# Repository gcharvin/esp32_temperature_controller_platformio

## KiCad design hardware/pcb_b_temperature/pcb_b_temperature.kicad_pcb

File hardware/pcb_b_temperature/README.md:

# PCB B v0.5 — buck 5 V intégré

Révision courante B0.5.3 du 10 novembre 2026. Ouvrir `pcb_b_temperature.kicad_pro`, puis le
schéma ou `pcb_b_temperature.kicad_pcb`. La carte garde **90 × 65 × 1,6 mm**,
deux couches externes de cuivre **70 µm**, les réserves de clips et les positions
des connecteurs conservés. A reste à v0.4.

## Alimentation

```text
J2 24V → F1 → Q2 anti-inversion → VIN_PROTECTED → J3 chauffage
                                   │
                                   └→ U1 LM2596 → L1 → +5V_BUCK → F2 1A → J1/A et logique B
                                                  │
                                                  └→ C10 → R13 → PGND

PGND puissance ── NT1, jonction cuivre près de l'entrée ── GND logique
```

| Repère | Élément | Empreinte / rôle |
| --- | --- | --- |
| U1 | LM2596S-5.0/NOPB | TO-263-5, languette **broche 3 / PGND** |
| L1 | Bourns SRP1770TA-101M, 100 µH | 16,9 × 16,9 mm, hauteur 7 mm |
| D9 | Vishay SS36-E3/57T, 60 V / 3 A | SMC, cathode sur BUCK_SW |
| C8 | Panasonic EEUFR1H101, 100 µF / 50 V | Condensateur d'entrée existant, déplacé ; Ø8 mm, pas 3,5 mm |
| C9 | 100 nF / 50 V X7R | 0805, découplage d'entrée local |
| C10 | Panasonic EEUFS1V331LB, 330 µF / 35 V | Ø8 mm nominal, pas formé 5 mm, hauteur maximale 16,5 mm ; dégagement Ø10 conservé |
| R13 | Vishay WSL1206R0500FEA, 50 mΩ / 1 % / 0,25 W | Empreinte locale `LabHardware:Vishay_WSL1206_6m_to_200m`, **dans le retour du condensateur C10**, pas en série avec la charge |
| NT1 | NetTie-2_SMD_Pad2.0mm | Cuivre de liaison des masses, exclu de la BOM d'assemblage |

La revue de fabrication adapte les pastilles R13 au dessin Vishay :
1,65 × 1,93 mm, centres espacés de 3,45 mm, intervalle intérieur 1,80 mm.
R13 est légèrement déplacée, de (20,5 ; 45) à (21 ; 44,5) mm dans le repère
local du PCB, pour dégager les zones de C10 et F2. Les pistes existantes restent
connectées dans les nouvelles plages. Les contrôles DRC et de démontage
mécanique ont été régénérés. Voir le [dossier de fabrication](../manufacturing/README.md)
et son plan d'assemblage pour les polarités et les coordonnées.

J8 et J9 et le module XL4015 sont supprimés. U1 a une sortie fixe 5 V : aucune
consigne à régler. Sa broche 5 ON/OFF est reliée à PGND ; le buck est activé
avec le 24 V. La limite étudiée est **0,8 A pour le système** ; F2 reste à 1 A.
La revue d'approvisionnement propose C9 **C0805C104K5RACTU** et R13
**WSL1206R0500FEA**. Leurs caractéristiques nominales correspondent aux
exigences ; disponibilité, pastilles recommandées et procédé restent à
approuver dans `../manufacturing/README.md` avant gel des MPN dans KiCad.

A reçoit toujours 5 V régulé. Les futures B pourront recevoir 12 V ou 5 V
avec leur propre adaptation d'alimentation ; cette B v0.5 n'est pas déclarée
multitension. Le démarrage du cœur du buck à 12 V est étudié séparément ;
aucune puissance de chauffage 100 W à 12 V/5 V n'est attribuée à cette carte.
Voir `../manufacturing/power_and_usb_review.md`.

Les masses gardent deux noms pour organiser leurs retours. NT1 les relie
électriquement près de l'entrée ; ce n'est pas une isolation. Le trajet du
chauffage jusqu'à J2 reste sur sa piste PGND de puissance, sans passer dans
NT1, les JST ou la DevKit. Les cinq trajets principaux de chauffage sont
contrôlés géométriquement et restent sans via discret.

## Placement, routage et contrôle

Le buck occupe la partie gauche et centrale de B. Plusieurs composants de
logique et voyants sont déplacés. Les JST A/B J1/J6/J7, la sonde J4 et les
borniers J2/J3 gardent leurs positions et brochages. `../placement.json` décrit
le placement courant et les hauteurs, sans enveloppes provisoires sans pads.

Le schéma natif, la BOM et le routage sont mis à jour ensemble. Résultat des
contrôles : **ERC 0 erreur / 0 avertissement, DRC 0 violation, 0 connexion
restante, 0 écart schéma/PCB**. Le rapport du buck et la conservation des
connecteurs sont dans `../review/routing/integrated_buck_validation.json`.
Les PDF de revue sont `../review/pcb_b_temperature.pdf` et
`../review/routing/pcb_b_temperature_routed.pdf`.

Le routage des boucles de commutation est explicite, avec un plan PGND local
sous la languette thermique. Les liaisons restantes ont été amorcées localement
avec Freerouting 1.9.0 en mode **un seul thread**, analytics désactivées, puis
corrigées et contrôlées dans KiCad. Aucune API de routage distante n'a reçu la
carte. Les scripts de migration sont des étapes historiques à appliquer à une
copie de v0.4 ; ils ne régénèrent pas les fichiers natifs livrés après édition.

## Simulation et limites

Le circuit de puissance reprend l'[étude LM2596](../power_study/lm2596/README.md) :
six essais d'acceptation complets sous ngspice, plus deux sensibilités ESR.
C8 fournit les 100 µF d'entrée étudiés ; C9 ajoute le découplage HF. Le banc
représente les ESR/DCR, mais pas les parasites des pistes, vias, connecteurs,
la protection amont ni le couplage du PWM chauffage. Le rattachement des nets
et les valeurs principales sont contrôlés sur la netlist exportée de B ; la
simulation n'est pas une extraction parasite du PCB routé.

La pointe de démarrage simulée approche **4,9 A dans L1**. Saturation réelle,
diode, fusibles, transitoires d'entrée, thermique, bruit sur la NTC et défauts
restent à vérifier sur prototype. Ce n'est pas un dossier libéré pour fabrication.
Le partage USB/VBUS et la mise à jour du firmware restent des sujets distincts.

**Mécanique :** le [STEP v0.8](../mechanical/README.md) représente maintenant ce
placement de B et ses hauteurs. Le berceau du XL4015 est retiré ; quatre pièces
imprimées et 17 étapes de montage/service passent les contrôles géométriques.
J1 reste proche de C10 : la fiche XHP documentée et sa marge passent, mais la
prise en main, les fils, la flexion des clips et la thermique exigent des essais
réels. Voir le [plan de mise au point](../review/routing/electronics_bench_plan.md).

Sources : [TI LM2596](https://www.ti.com/lit/ds/symlink/lm2596.pdf),
[Bourns SRP1770TA](https://www.bourns.com/docs/Product-Datasheets/srp1770ta.pdf),
[Vishay SS36](https://www.vishay.com/docs/88751/ss32.pdf),
[Panasonic C10](https://industrial.panasonic.com/ww/products/pt/aluminum-cap-lead/models/EEUFS1V331LB).

La préparation3 fige les MPN dans KiCad, emploie les pastilles Kingbright pour les voyants et décale D7 de0,25mm en Y pour dégager SDA. Les borniers sont modélisés à14mm de hauteur enveloppe. Les valeurs électriques et les pistes sont conservées. Les instructions de câblage, de test et d’assemblage sont dans le dossier de fabrication.

## Révision diagnostic du 6 novembre 2026

Les pastilles TP au dos sont du cuivre seul, sans pâte ni pièce à acheter.
Voir [le plan de mesure](../TEST_POINTS.md) et le firmware autonome dans
`../../firmware/diagnostic/`. Les pistes antérieures et le circuit de puissance
sont conservés ; le diagnostic maintient ENABLE à zéro.

## Extension UART du 10 novembre 2026

Révisions **A0.4.3 / B0.5.3** : J10 est un JST-XH3 supplémentaire assemblé
sur chaque PCB, pas2,50mm, même MPN B3B-XH-A(LF)(SN) que J6.

| Broche J10 | Carte A | Carte B température |
| --- | --- | --- |
| 1 | GND | GND |
| 2 | TX_A, GPIO17, pad U1.22 | Non connectée ; réserve RX de future B |
| 3 | RX_A, GPIO16, pad U1.21 | Non connectée ; réserve TX de future B |

Câblage **droit 1→1, 2→2, 3→3** ; TX/RX sont nommés du point de vue de A.
UART logique **3,3V**, sans alimentation dans ce connecteur : jamais RS232
ni5V directement. Les transceivers RS232/RS485 éventuels appartiennent aux
futures B. Le port série USB de la DevKit reste indépendant ; les deux PWM
et ENABLE/FAULT_N/DIN0 restent disponibles. GPIO16/17 doivent être libres
sur la variante de DevKit employée (modules à PSRAM utilisant ces broches
non couverts par cette interface). Aucun UART n’est activé par le firmware
de diagnostic actuel ; aucun essai de boucle matérielle n’est déclaré fait.

B température n’a pas de périphérique UART : les deux pastilles sont
intentionnellement NC et le connecteur est néanmoins à souder. Le câble UART
est **facultatif pour ce prototype** et n’est pas ajouté au devis LCSC en cours.
Si nécessaire plus tard, reprendre la construction H02 XHP-3/XHP-3,300mm AWG26
avec un repérage UART distinct. Ne pas confondre J6 I²C et J10 UART, mécaniquement
identiques. Les alias fabricant J8/J9 des deux sockets de A restent inchangés.

## B0.5.3 : variantes du devis intégrées

C10 utilise maintenant `LabHardware:CP_Radial_EEUFS1V331LB_P5_D10_Keepout` :
les pastilles, trous et dégagement Ø10 antérieurs sont conservés ; le modèle
3D local a une hauteur maximale de 16,5 mm. R13 = 50 mΩ dans le retour de C10.
D8 HEAT est jaune ; ses pastilles et sa résistance de 2,2 kΩ sont conservées.
Les sept essais électriques de la combinaison FS/50 mΩ passent ; voir
`../power_study/lm2596/current_acceptance.json`. Le STEP courant est v12.
Les pistes, vias, UUID de pastilles, positions et nets n'ont pas changé.

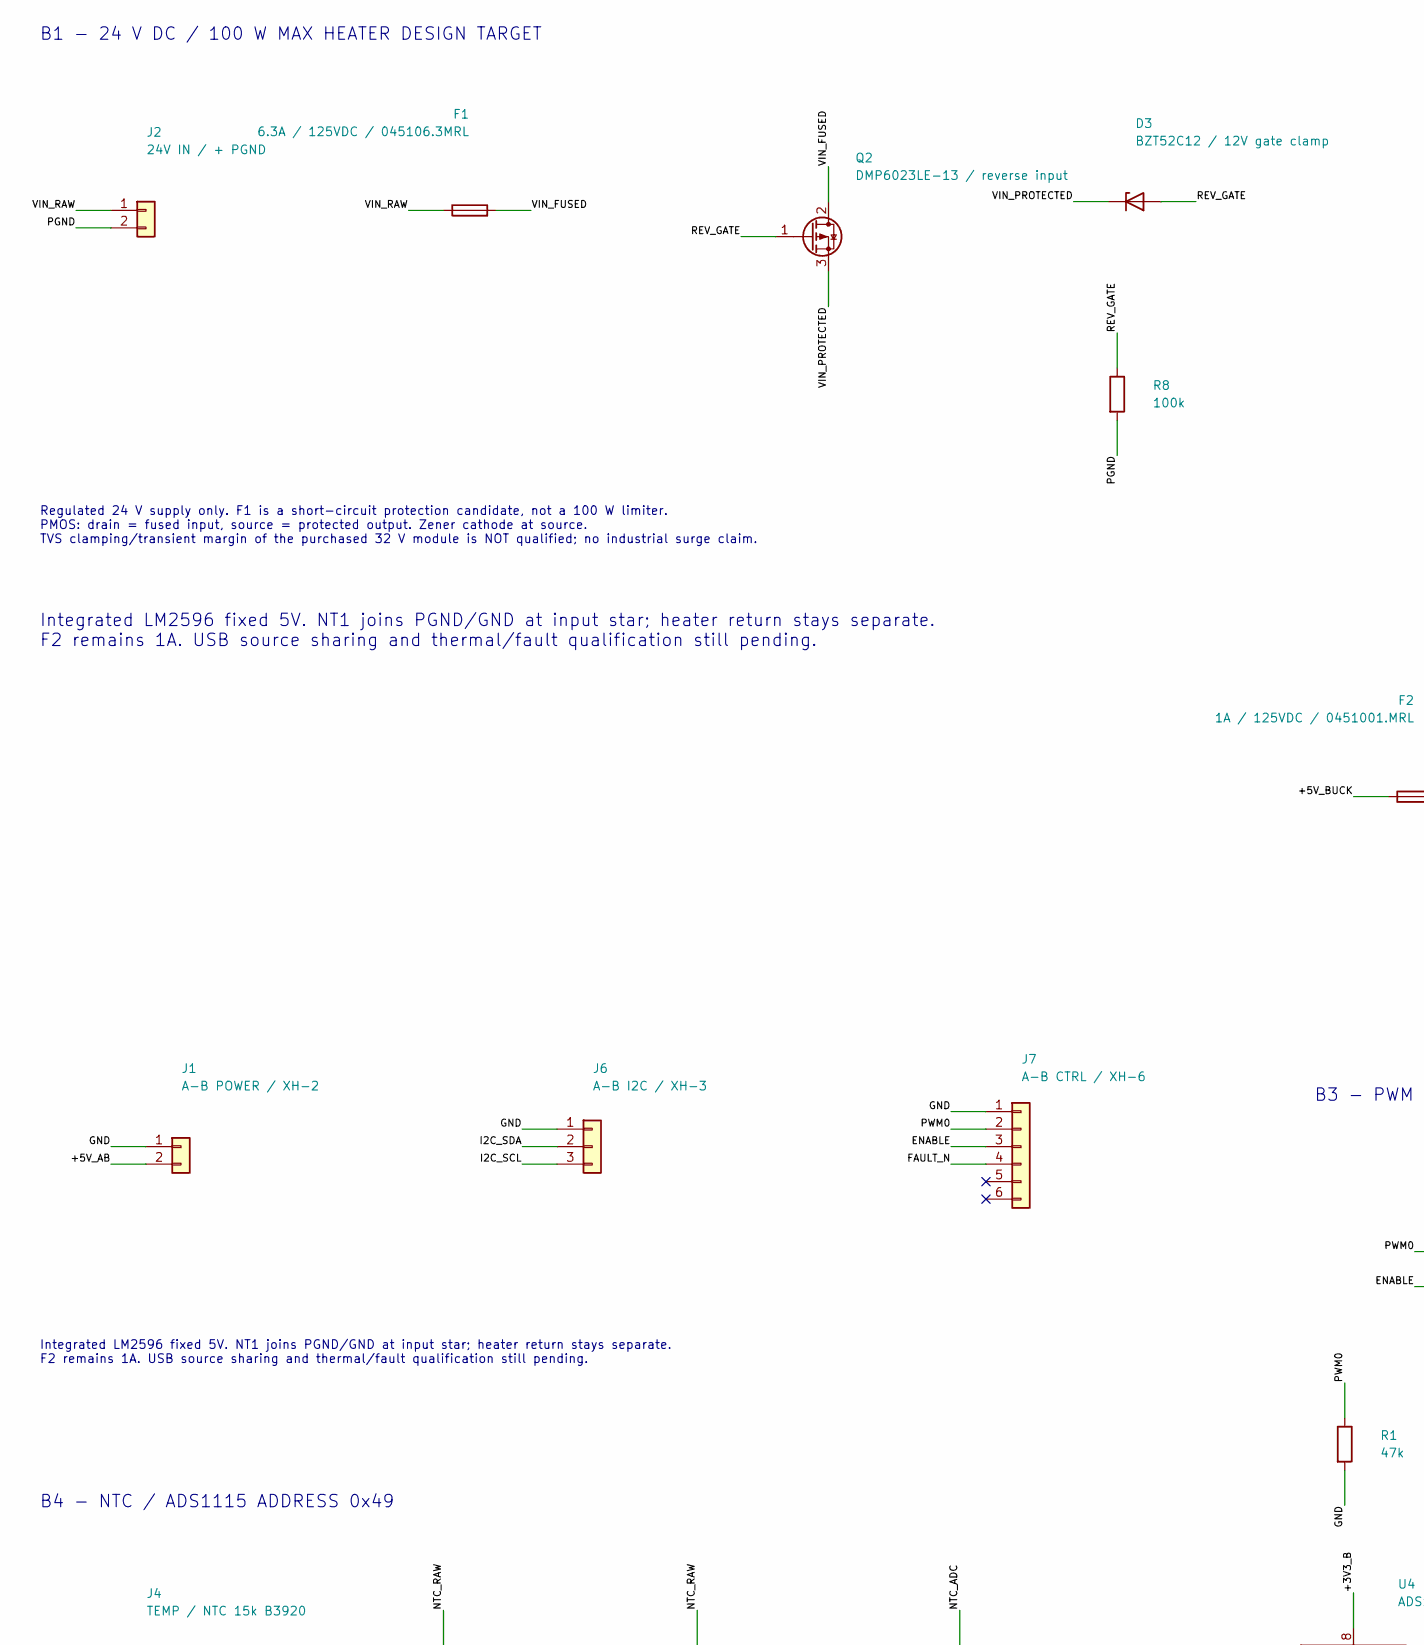
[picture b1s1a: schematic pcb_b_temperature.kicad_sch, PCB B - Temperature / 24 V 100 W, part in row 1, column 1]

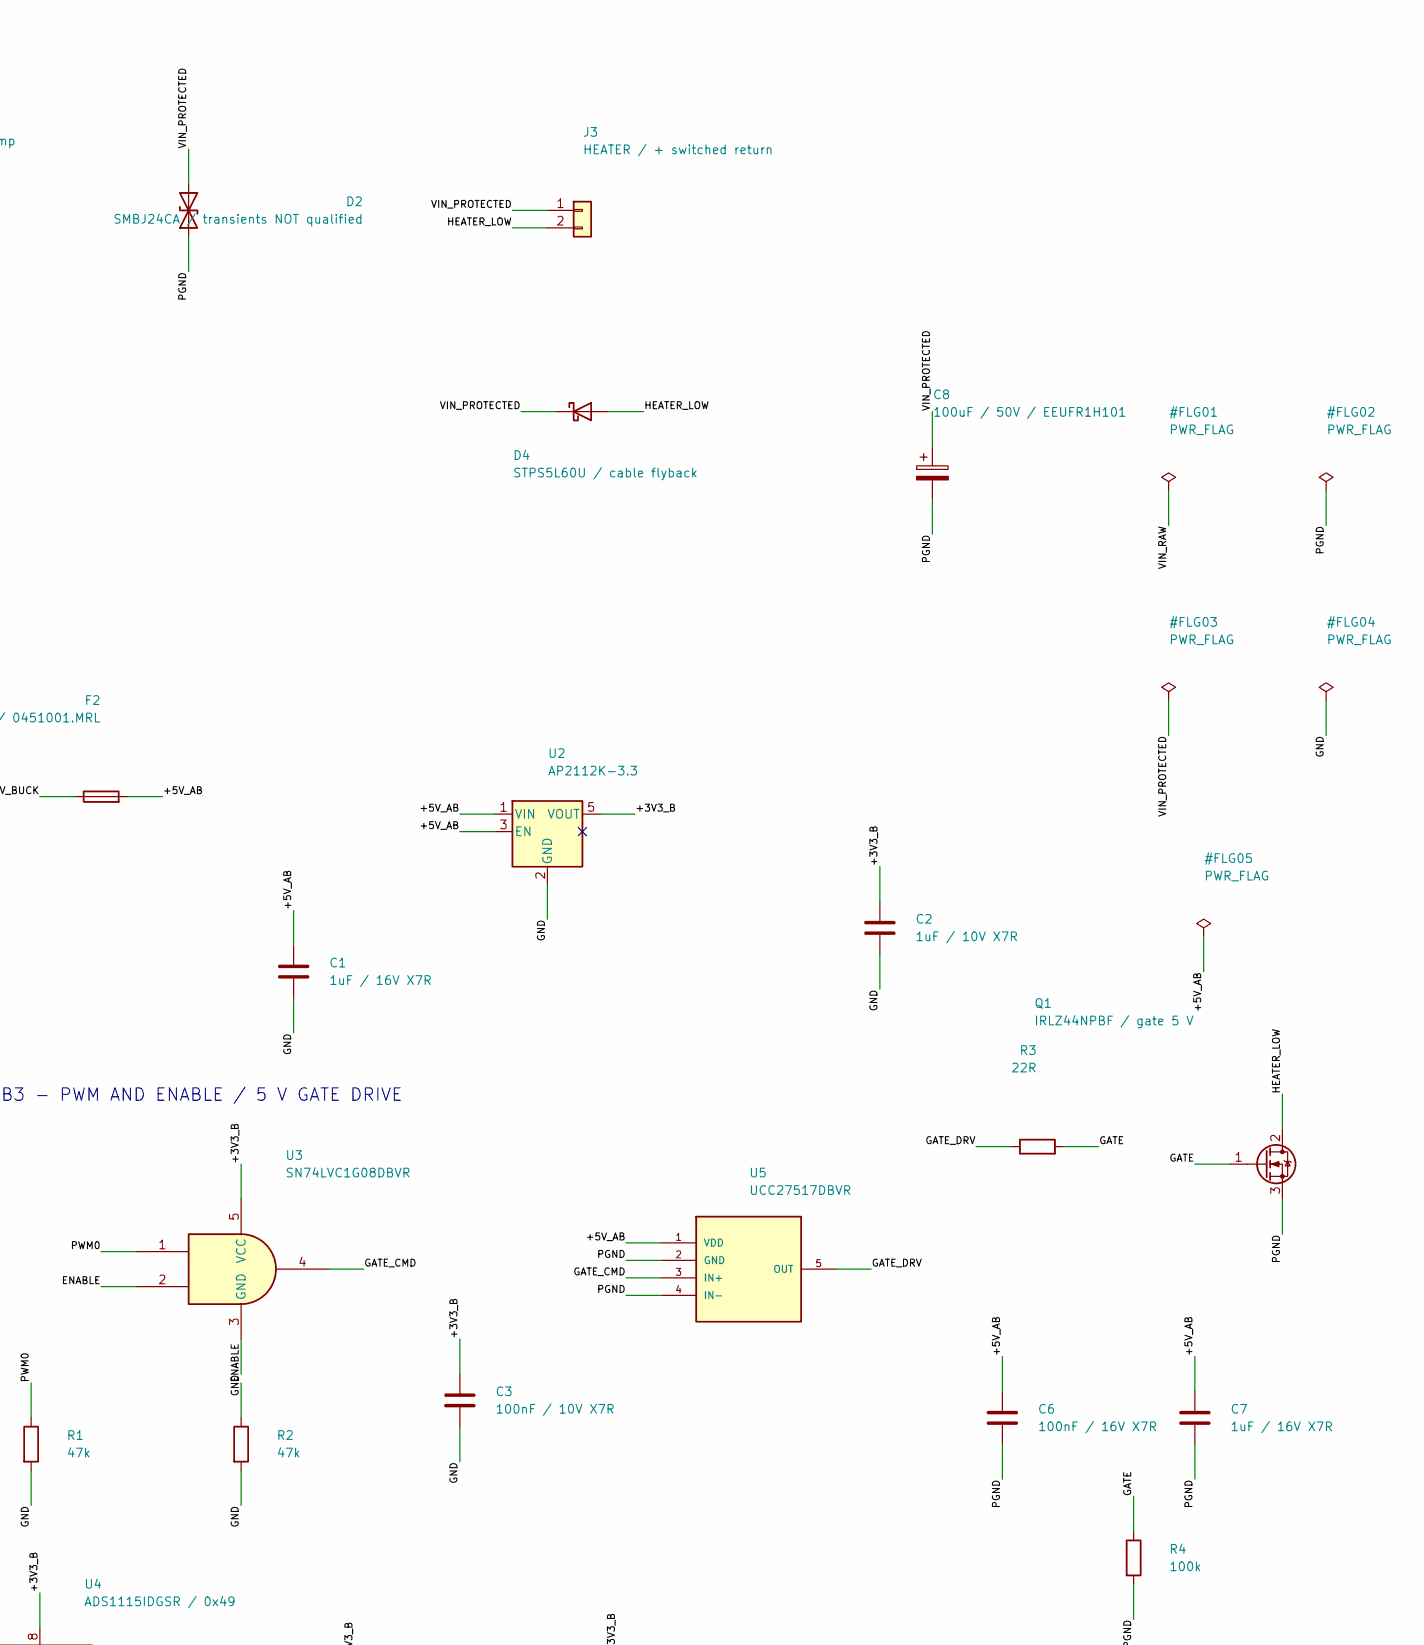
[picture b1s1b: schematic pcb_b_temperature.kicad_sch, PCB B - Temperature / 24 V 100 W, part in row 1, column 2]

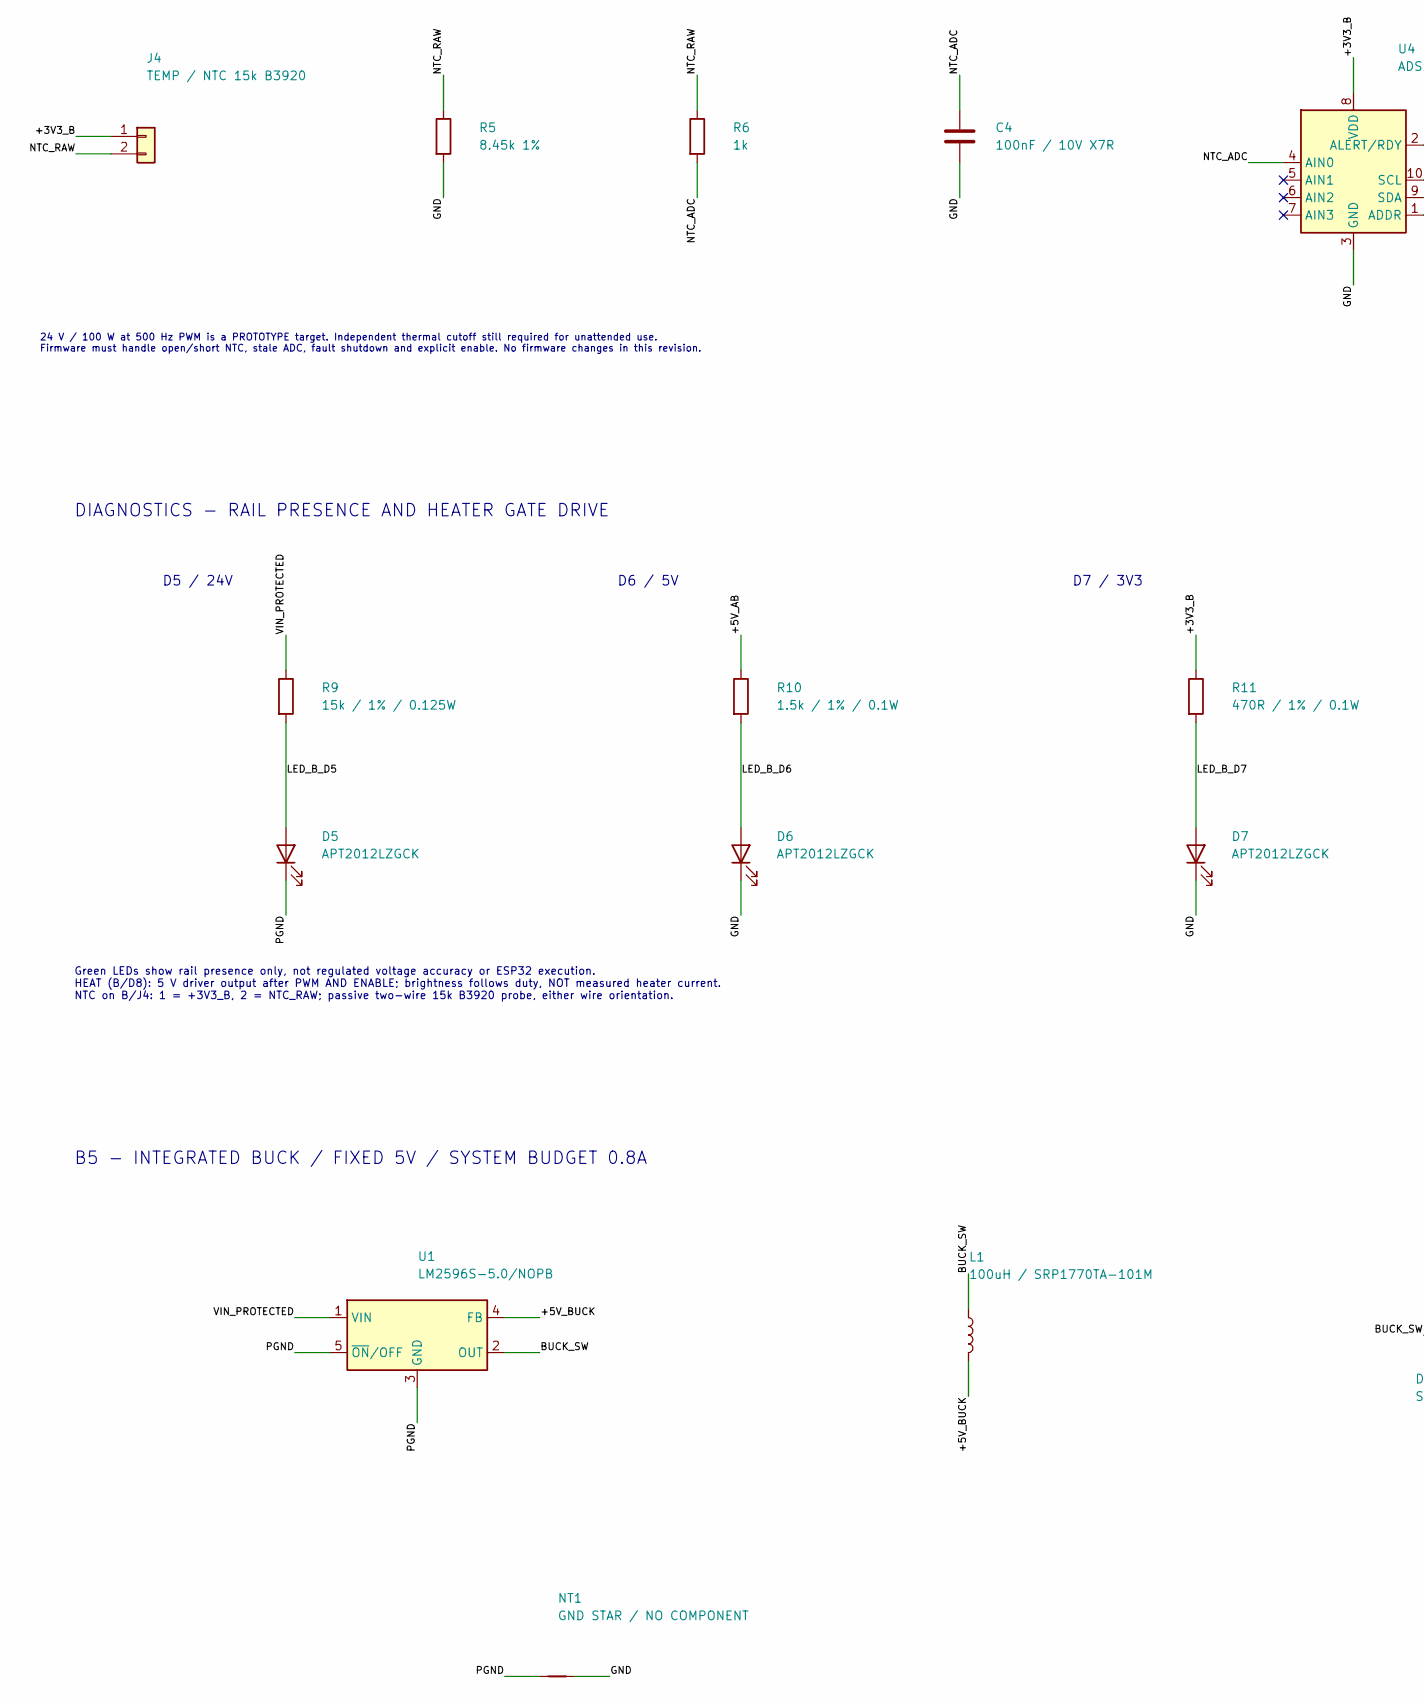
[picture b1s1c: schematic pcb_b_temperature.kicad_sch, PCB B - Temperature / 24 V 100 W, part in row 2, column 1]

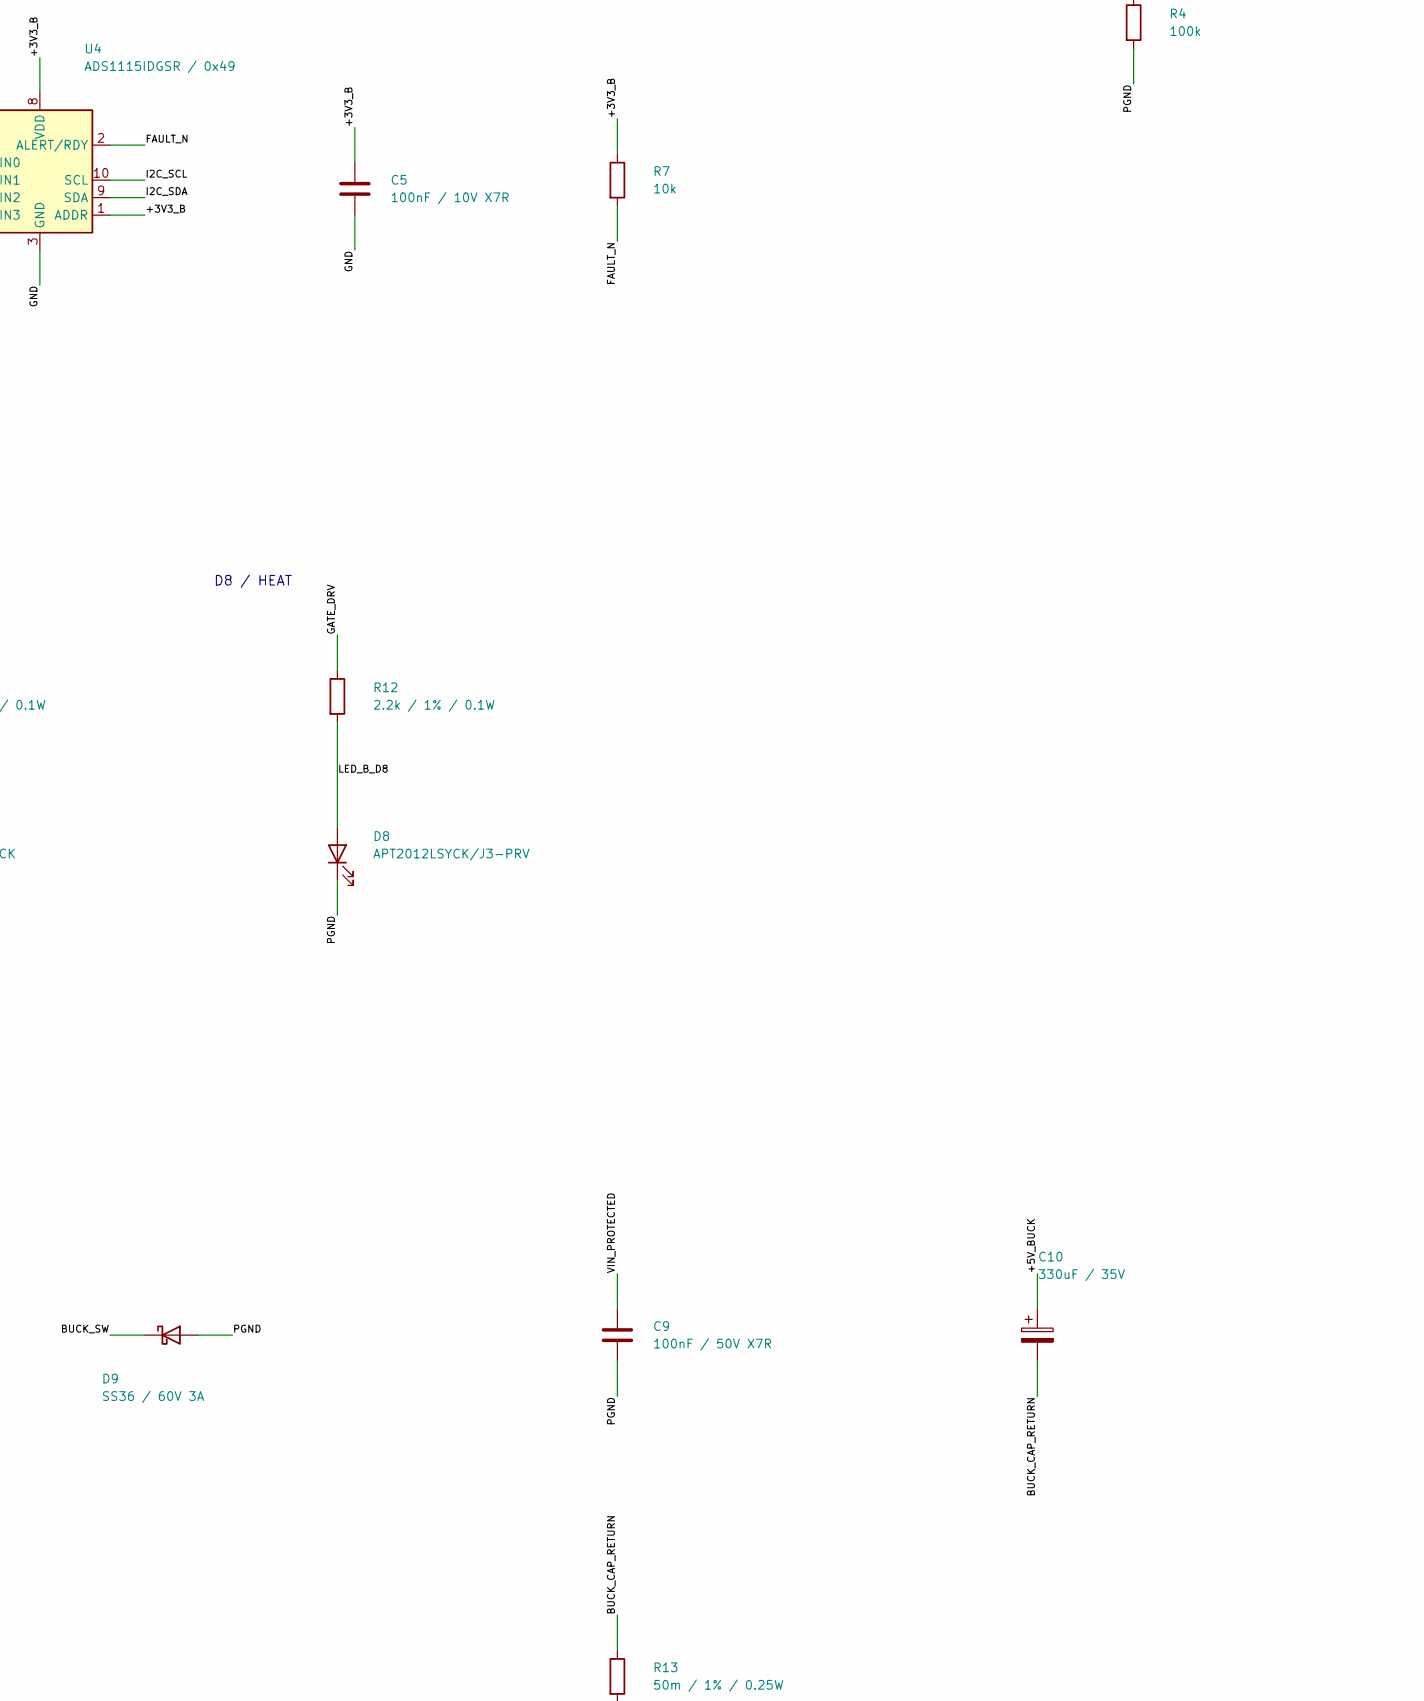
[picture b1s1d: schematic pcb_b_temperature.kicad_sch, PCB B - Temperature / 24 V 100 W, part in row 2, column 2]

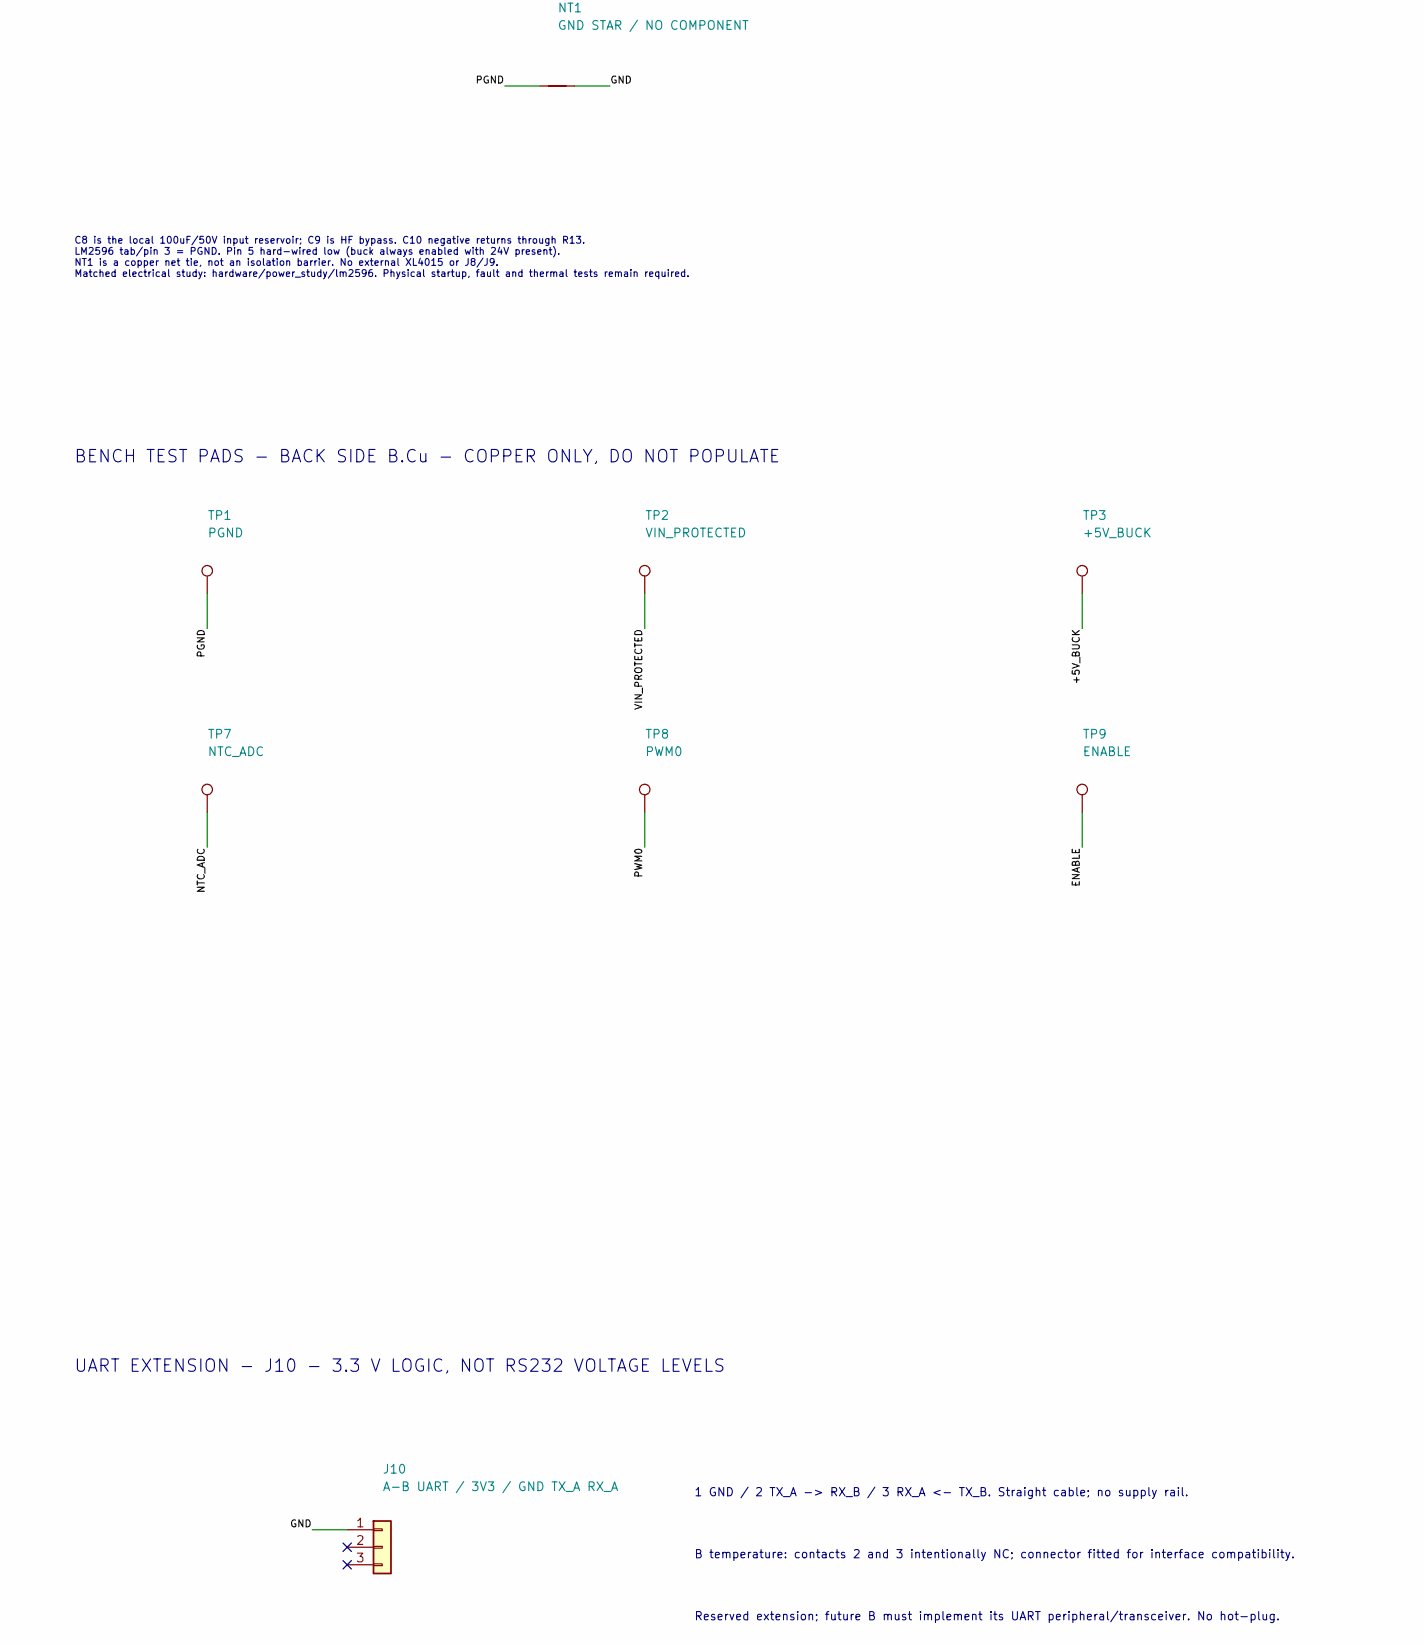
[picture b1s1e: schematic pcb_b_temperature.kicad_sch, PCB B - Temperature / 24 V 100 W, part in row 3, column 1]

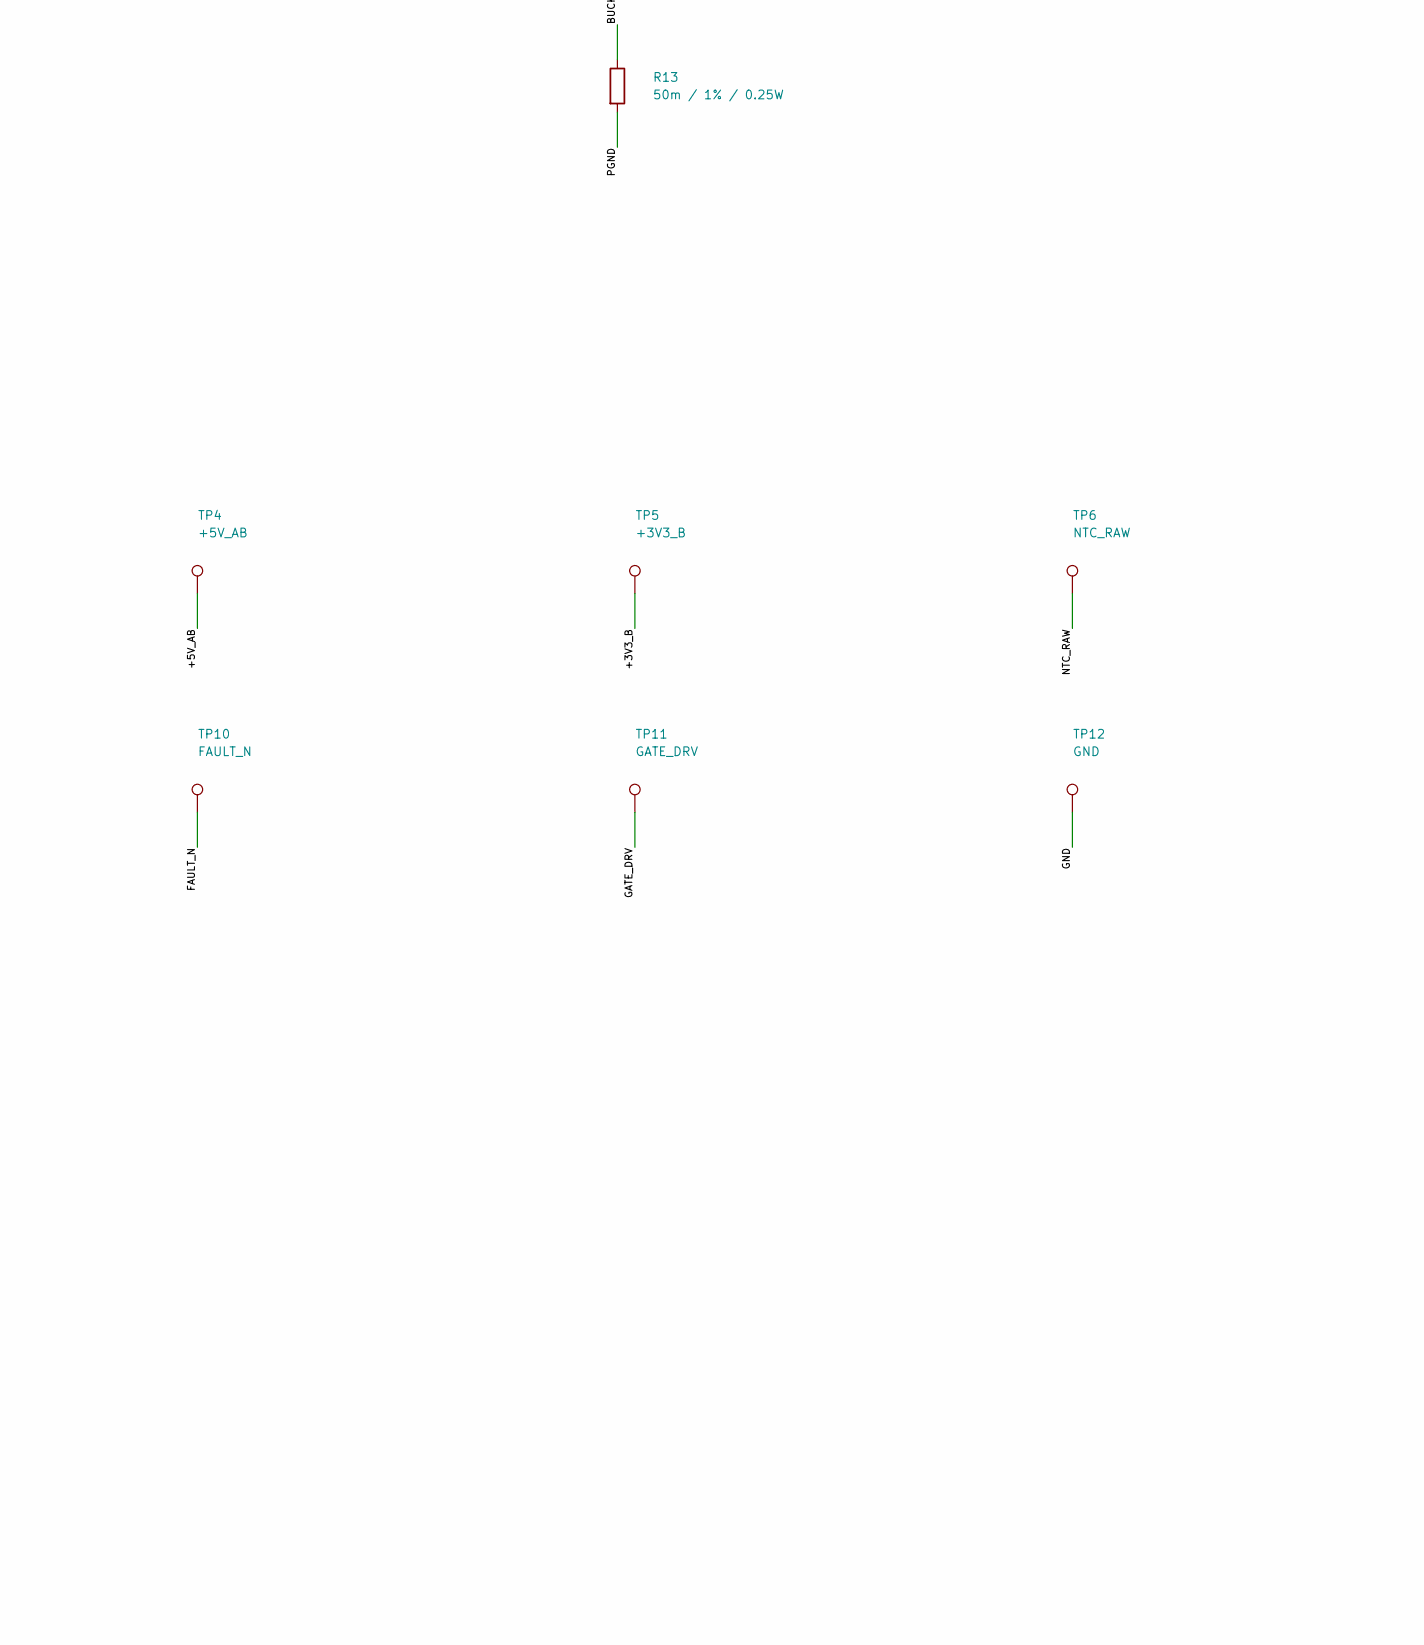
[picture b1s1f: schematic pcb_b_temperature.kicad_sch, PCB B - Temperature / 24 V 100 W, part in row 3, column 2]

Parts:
C1, C7: 1uF / 16V X7R; C_0603_1608Metric; MPN 0603B105K160CT
C2: 1uF / 10V X7R; C_0603_1608Metric; MPN 0603B105K160CT
C3, C4, C5: 100nF / 10V X7R; C_0603_1608Metric; MPN C0603C104K4RACTU
C6: 100nF / 16V X7R; C_0603_1608Metric; MPN C0603C104K4RACTU
C8: 100uF / 50V / EEUFR1H101; CP_Radial_D8.0mm_P3.50mm; MPN EEUFR1H101
C9: 100nF / 50V X7R; C_0805_2012Metric; MPN C0805C104K5RACTU
C10: 330uF / 35V; CP_Radial_EEUFS1V331LB_P5_D10_Keepout; MPN EEUFS1V331LB
D2: SMBJ24CA / transients NOT qualified; D_SMB; MPN SMBJ24CA
D3: BZT52C12 / 12V gate clamp; D_SOD-123; MPN BZT52C12-7-F
D4: STPS5L60U / cable flyback; D_SMB; MPN STPS5L60U
D5, D6, D7: APT2012LZGCK; LED_Kingbright_APT2012_Manufacturer; MPN APT2012LZGCK
D8: APT2012LSYCK/J3-PRV; LED_Kingbright_APT2012_Manufacturer; MPN APT2012LSYCK/J3-PRV
D9: SS36 / 60V 3A; D_SMC; MPN SS36-E3/57T
F1: 6.3A / 125VDC / 045106.3MRL; Fuse_Littelfuse-NANO2-451_453; MPN 045106.3MRL
F2: 1A / 125VDC / 0451001.MRL; Fuse_Littelfuse-NANO2-451_453; MPN 0451001.MRL
J1: A-B POWER / XH-2; JST_XH_B2B-XH-A_1x02_P2.50mm_Vertical; MPN B2B-XH-A(LF)(SN)
J2: 24V IN / + PGND; TerminalBlock_Phoenix_MKDS-1,5-2-5.08_1x02_P5.08mm_Horizont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; MPN 1715721
J3: HEATER / + switched return; TerminalBlock_Phoenix_MKDS-1,5-2-5.08_1x02_P5.08mm_Horizont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; MPN 1715721
J4: TEMP / NTC 15k B3920; JST_XH_B2B-XH-A_1x02_P2.50mm_Vertical; MPN B2B-XH-A(LF)(SN)
J6: A-B I2C / XH-3; JST_XH_B3B-XH-A_1x03_P2.50mm_Vertical; MPN B3B-XH-A(LF)(SN)
J7: A-B CTRL / XH-6; JST_XH_B6B-XH-A_1x06_P2.50mm_Vertical; MPN B6B-XH-A(LF)(SN)
J10: A-B UART / 3V3 / GND TX_A RX_A; JST_XH_B3B-XH-A_1x03_P2.50mm_Vertical; MPN B3B-XH-A(LF)(SN)
L1: 100uH / SRP1770TA-101M; L_Bourns_SRP1770TA_16.9x16.9mm; MPN SRP1770TA-101M
NT1: GND STAR / NO COMPONENT; NetTie-2_SMD_Pad2.0mm
Q1: IRLZ44NPBF / gate 5 V; TO-220-3_Vertical; MPN IRLZ44NPBF
Q2: DMP6023LE-13 / reverse input; SOT-223-3_TabPin2; MPN DMP6023LE-13
R1, R2: 47k; R_0603_1608Metric; MPN RC0603FR-0747KL
R3: 22R; R_0603_1608Metric; MPN RC0603FR-0722RL
R4, R8: 100k; R_0603_1608Metric; MPN RC0603FR-07100KL
R5: 8.45k 1%; R_0603_1608Metric; MPN RC0603FR-078K45L
R6: 1k; R_0603_1608Metric; MPN RC0603FR-071KL
R7: 10k; R_0603_1608Metric; MPN RC0603FR-0710KL
R9: 15k / 1% / 0.125W; R_0805_2012Metric; MPN RC0805FR-0715KL
R10: 1.5k / 1% / 0.1W; R_0603_1608Metric; MPN RC0603FR-071K5L
R11: 470R / 1% / 0.1W; R_0603_1608Metric; MPN RC0603FR-07470RL
R12: 2.2k / 1% / 0.1W; R_0603_1608Metric; MPN RC0603FR-072K2L
R13: 50m / 1% / 0.25W; Vishay_WSL1206_6m_to_200m; MPN WSL1206R0500FEA
TP1: PGND; ProbePad_D1.5mm_NoPaste
TP2: VIN_PROTECTED; ProbePad_D1.5mm_NoPaste
TP3: +5V_BUCK; ProbePad_D1.5mm_NoPaste
TP4: +5V_AB; ProbePad_D1.5mm_NoPaste
TP5: +3V3_B; ProbePad_D1.5mm_NoPaste
TP6: NTC_RAW; ProbePad_D1.5mm_NoPaste
TP7: NTC_ADC; ProbePad_D1.5mm_NoPaste
TP8: PWM0; ProbePad_D1.5mm_NoPaste
TP9: ENABLE; ProbePad_D1.5mm_NoPaste
TP10: FAULT_N; ProbePad_D1.5mm_NoPaste
TP11: GATE_DRV; ProbePad_D1.5mm_NoPaste
TP12: GND; ProbePad_D1.5mm_NoPaste
U1: LM2596S-5.0/NOPB; TO-263-5_TabPin3; MPN LM2596S-5.0/NOPB
U2: AP2112K-3.3; SOT-23-5; MPN AP2112K-3.3TRG1
U3: SN74LVC1G08DBVR; SOT-23-5; MPN SN74LVC1G08DBVR
U4: ADS1115IDGSR / 0x49; TSSOP-10_3x3mm_P0.5mm; MPN ADS1115IDGSR
U5: UCC27517DBVR; SOT-23-5; MPN UCC27517DBVR

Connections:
/+3V3_B: C2.1, C3.1, C5.1, J4.1, R7.1, R11.1, TP5.1, U2.5 (VOUT), U3.5 (VCC), U4.1 (ADDR), U4.8 (VDD)
/+5V_AB: C1.1, C6.1, C7.1, F2.2, J1.2, R10.1, TP4.1, U2.1 (VIN), U2.3 (EN), U5.1 (VDD)
/+5V_BUCK: C10.1, F2.1, L1.2, TP3.1, U1.4 (FB)
/BUCK_CAP_RETURN: C10.2, R13.1
/BUCK_SW: D9.1 (K), L1.1, U1.2 (OUT)
/ENABLE: J7.3, R2.1, TP9.1, U3.2
/FAULT_N: J7.4, R7.2, TP10.1, U4.2 (ALERT/RDY)
/GATE: Q1.1 (G), R3.2, R4.1
/GATE_CMD: U3.4, U5.3 (IN+)
/GATE_DRV: R3.1, R12.1, TP11.1, U5.5 (OUT)
/GND: C1.2, C2.2, C3.2, C4.2, C5.2, D6.1 (K), D7.1 (K), J1.1, J6.1, J7.1, J10.1, NT1.2, R1.2, R2.2, R5.2, TP12.1, U2.2 (GND), U3.3 (GND), U4.3 (GND)
/HEATER_LOW: D4.2 (A), J3.2, Q1.2 (D)
/I2C_SCL: J6.3, U4.10 (SCL)
/I2C_SDA: J6.2, U4.9 (SDA)
/LED_B_D5: D5.2 (A), R9.2
/LED_B_D6: D6.2 (A), R10.2
/LED_B_D7: D7.2 (A), R11.2
/LED_B_D8: D8.2 (A), R12.2
/NTC_ADC: C4.1, R6.2, TP7.1, U4.4 (AIN0)
/NTC_RAW: J4.2, R5.1, R6.1, TP6.1
/PGND: C6.2, C7.2, C8.2, C9.2, D2.1 (A1), D5.1 (K), D8.1 (K), D9.2 (A), J2.2, NT1.1, Q1.3 (S), R4.2, R8.2, R13.2, TP1.1, U1.3 (GND), U1.5 (~ON/OFF), U5.2 (GND), U5.4 (IN-)
/PWM0: J7.2, R1.1, TP8.1, U3.1
/REV_GATE: D3.2 (A), Q2.1 (G), R8.1
/VIN_FUSED: F1.2, Q2.2 (D)
/VIN_PROTECTED: C8.1, C9.1, D2.2 (A2), D3.1 (K), D4.1 (K), J3.1, Q2.3 (S), R9.1, TP2.1, U1.1 (VIN)
/VIN_RAW: F1.1, J2.1

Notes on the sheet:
B1 - 24 V DC / 100 W MAX HEATER DESIGN TARGET
Regulated 24 V supply only. F1 is a short-circuit protection candidate, not a 100 W limiter. PMOS: drain = fused input, source = protected output. Zener cathode at source. TVS clamping/transient margin of the purchased 32 V module is NOT qualified; no industrial surge claim.
Integrated LM2596 fixed 5V. NT1 joins PGND/GND at input star; heater return stays separate. F2 remains 1A. USB source sharing and thermal/fault qualification still pending.
B3 - PWM AND ENABLE / 5 V GATE DRIVE
B4 - NTC / ADS1115 ADDRESS 0x49
24 V / 100 W at 500 Hz PWM is a PROTOTYPE target. Independent thermal cutoff still required for unattended use. Firmware must handle open/short NTC, stale ADC, fault shutdown and explicit enable. No firmware changes in this revision.
DIAGNOSTICS - RAIL PRESENCE AND HEATER GATE DRIVE
D5 / 24V
D6 / 5V
D7 / 3V3
D8 / HEAT
Green LEDs show rail presence only, not regulated voltage accuracy or ESP32 execution. HEAT (B/D8): 5 V driver output after PWM AND ENABLE; brightness follows duty, NOT measured heater current. NTC on B/J4: 1 = +3V3_B, 2 = NTC_RAW; passive two-wire 15k B3920 probe, either wire orientation.
B5 - INTEGRATED BUCK / FIXED 5V / SYSTEM BUDGET 0.8A
C8 is the local 100uF/50V input reservoir; C9 is HF bypass. C10 negative returns through R13. LM2596 tab/pin 3 = PGND. Pin 5 hard-wired low (buck always enabled with 24V present). NT1 is a copper net tie, not an isolation barrier. No external XL4015 or J8/J9. Matched electrical study: hardware/powe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
BENCH TEST PADS - BACK SIDE B.Cu - COPPER ONLY, DO NOT POPULATE
UART EXTENSION - J10 - 3.3 V LOGIC, NOT RS232 VOLTAGE LEVELS
1 GND / 2 TX_A -> RX_B / 3 RX_A <- TX_B. Straight cable; no supply rail.
B temperature: contacts 2 and 3 intentionally NC; connector fitted for interface compatibility.
Reserved extension; future B must implement its UART peripheral/transceiver. No hot-plug.
